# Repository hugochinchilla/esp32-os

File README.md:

# Chinchilla (esp32-os)

A 90s-style desktop operating environment (think Windows 95/98) for the
ESP32-S3, with VGA output from GPIO pins, Wi-Fi, and USB keyboard and mouse.

Status: **the desktop runs on the board.** Overlapping, resizable windows in
the 98 look with menus, a taskbar with a clock and the Start menu, desktop
icons, widgets, an Editor, a File manager, a Picture viewer (BMP, PNG,
baseline JPEG, GIF) and a drawing program, files on the flash (LittleFS, kept across restarts), a
start-up self-test, plus a debug protocol for screenshots,
injected input and file transfer.

## Try it in the browser

**<https://www.hugochinchilla.net/esp32-os/>**

The same desktop, running in a web page with nothing to install. It needs a
mouse and a keyboard. Files saved on its C: stay in your own browser. It is
built from `main` on every change; how it works is under
[Chinchilla in a web browser](#chinchilla-in-a-web-browser).

## What it will be

- 640x480 at 60 Hz on a VGA monitor, 256 colours, with a mouse cursor that
  always moves at 60 Hz.
- A desktop with taskbar, Start menu, icons and overlapping windows.
- A file system with a file manager, a Notepad-style text editor, and a viewer
  for BMP, PNG, JPEG and GIF images.
- Wi-Fi, with the clock set from NTP, or from an optional battery-backed clock
  chip.
- Vizcacha, a web browser for pages as the 1990s wrote them: no scripts, no
  style sheets, plain HTTP. [FrogFind](http://frogfind.com/) is its way into
  today's web.
- A serial debug protocol (screen capture, injected keyboard and mouse events)
  so the OS can be tested by an agent without a human.
- Remote keyboard, mouse and screen over the network until USB input hardware
  exists.

## Hardware

- ESP32-S3 dev board with 16 MB flash and 8 MB octal PSRAM (ESP32-S3-N16R8,
  DevKitC-1 pin layout, two USB-C sockets).
- An adapter board built on a 5x7 cm perfboard that the dev board plugs into:
  9 colour resistors and 2 sync resistors for VGA, an audio output filter for a
  3.5 mm jack, and a beeper.

See [docs/hardware/README.md](docs/hardware/README.md) for the pin map, the
resistor values and build notes.

## Repository layout

| Path | Contents |
| --- | --- |
| `docs/DECISIONS.md` | The index of what has been decided, what was rejected, and what is still open: what always applies, and one line per decision |
| `docs/decisions/` | One file per decision, listed in the index by `tools/decisions_index.py` |
| `docs/hardware/` | VGA adapter pin map, resistor values and board diagram |
| `docs/debug-protocol.md` | The serial protocol for screenshots and injected input |
| `docs/benchmark.md` | How to run the 60 fps benchmark again and read its results |
| `core/` | The portable part of the OS (C++). Depends on no hardware; builds for the board and for a PC |
| `firmware/os/` | The OS firmware: ESP-IDF project with the ESP32 adapters for `core/` |
| `firmware/vga-test/` | ESP-IDF test program for the VGA wiring |
| `host/` | PC build: unit tests and picture tests for `core/`, a simulated board, and `desktop/`, Chinchilla as a desktop program for Linux |
| `third_party/` | Freely licensed files from elsewhere: the Spleen font; the engine of Doom (GPL 2), which is part of `programs/doom` only |
| `web/` | Chinchilla in a web browser: the Emscripten build of `host/desktop/` and its page |
| `ci/` | GitHub Actions workflows to copy into `.github/workflows/`: the build, publishing the browser version on GitHub Pages, and deploying its relay to Cloudflare |
| `tools/` | `dbg.py`, the debug tool; `check_pictures.py`, the picture tests; `gen_font.py`, the font table generator; `mockup/`, the script that drew the target look; the setup script for Arch-based systems; the script that regenerates the board diagram |

## Tests on the PC

No board needed. Requires CMake, a C++ compiler, Python 3 and pyserial.

```sh
cmake -S host -B build/host
cmake --build build/host
ctest --test-dir build/host --output-on-failure
```

`build/host/sim` is a simulated board: it prints a port name that
`tools/dbg.py --port <name>` can talk to. `build/host/sim <folder>` also shows
that folder of the PC as drive D:.

The picture tests draw the desktop through a series of steps and compare
each screen with `host/tests/pictures/`. After an intended change to the
look, regenerate them, look at every changed picture, and commit them:

```sh
python3 tools/check_pictures.py build/host/render_scenes --update
```

The font table `core/src/gfx/font_spleen6x12.cpp` is generated:
`python3 tools/gen_font.py third_party/fonts/spleen/spleen-6x12.bdf core/src/gfx/font_spleen6x12.cpp`.

## The command shell on a PC

Chinchilla's command shell (`dir`, `ls`, `type`, `copy`, `ps`, `kill`...) in
a terminal of the PC. It is the same code that will run on the board's serial
port and in a terminal window; here the PC's terminal is the device. Needs
only CMake and a C++ compiler.

```sh
cmake -S host -B build/host && cmake --build build/host --target chinchilla-console
build/host/chinchilla-console                 # C: is a RAM disk with the sample files
build/host/chinchilla-console ~/some/folder   # that folder is C:, for real
```

`help` lists the commands. The line editing, the up arrow and Ctrl+C are
Chinchilla's own, not the PC's. Ctrl+D or `exit` leaves.

## Chinchilla as a desktop program (Linux)

The same `core/` in a window on a PC: the window is the monitor, the PC's
mouse and keyboard are the board's, and a folder of the PC is drive C:. For
trying programs without flashing, and for showing Chinchilla to someone with
no board. It is not an emulator of the ESP32: no memory limits, no real
Wi-Fi, and far faster than the board, so it says nothing about speed, RAM or
the colours on a real monitor.

Needs CMake, a C++ compiler and SDL2 with its headers:

| System | Install |
| --- | --- |
| Arch, Omarchy | `sudo pacman -S --needed cmake gcc make sdl2` (on a current Arch this installs `sdl2-compat`) |
| Debian, Ubuntu | `sudo apt install cmake g++ make libsdl2-dev` |
| Fedora | `sudo dnf install cmake gcc-c++ make SDL2-devel` |

```sh
cmake -S host -B build/desktop -DHOST_SANITIZE=OFF -DCMAKE_BUILD_TYPE=Release
cmake --build build/desktop --target chinchilla
build/desktop/chinchilla
```

The result is one file of about 1 MB, `build/desktop/chinchilla`. It runs on
another Linux PC with the same kind of processor that has SDL2 installed
(most desktops do).

| Option | What it does |
| --- | --- |
| `--drive FOLDER` | The folder that is drive C:. Default `~/.local/share/chinchilla/C`. A new, empty folder gets the sample files. They are ordinary files: copy a picture in from Linux and the File manager shows it |
| `--fast` | No start-up screens (a key or a click also skips them) |
| `--scale N` | Open the window at N times 640x480. Default: the largest of 1, 2, 3 that fits the desktop |
| `--fullscreen` | Start on the whole screen |
| `--mute` | No sound. Without it the self-test ends in a beep, the desktop comes up with a chime and message boxes knock, through the PC's sound card |

In the window:

- The window can be any size. The picture keeps its 4:3 shape, with black
  bars where it does not fill the window.
- F11 switches between the window and the whole screen. F12 saves a picture
  of the window as `chinchilla-001.bmp`, `-002` and so on in the folder the
  program was started from.
- Ctrl+Alt+End is Chinchilla's Ctrl+Alt+Del (Linux keeps the real one), and
  Ctrl+Esc opens the Start menu if the desktop keeps the Super key (which
  also means Super+D, Chinchilla's "show the desktop", may not arrive).
- Keys type what a US keyboard would: the core has no other layouts yet,
  the same as on the board.
- Closing the window shuts Chinchilla down: programs are asked to close, so
  the Editor still asks about unsaved text. Closing it again within three
  seconds leaves at once.
- There is no sound: the system does not make any yet, on the board either.

`build/host/chinchilla`, built along with the tests when SDL2 is installed,
is the same program with the memory checks on: some ten times larger, and
slower.

## Chinchilla in a web browser

The desktop program again, built to WebAssembly: a page that anyone can open,
with nothing to install. The page is the monitor, C: is kept in the visitor's
own browser (nothing is sent anywhere), and it comes back on the next visit.
It needs a mouse and a keyboard; it is not made for phones.

Needs [Emscripten](https://emscripten.org/docs/getting_started/downloads.html)
(tested with 7.0.0) and CMake. Emscripten downloads its own SDL2 the first
time.

```sh
emcmake cmake -S web -B build/web
cmake --build build/web
python3 -m http.server -d build/web/site 8080    # then open http://localhost:8080/
```

The result is one file, `build/web/site/index.html` (about 1.7 MB, 0.6 MB as
web servers send it). Put it on any web server, or send the file itself: it
also works opened straight from a folder.

To publish it on GitHub Pages on every change to `main`, copy
`ci/github-pages-workflow.yml` to `.github/workflows/pages.yml` and choose
Settings > Pages > Source: "GitHub Actions". The address is then
`https://<owner>.github.io/<repository>/`.

The page reaches the web through a relay, because a page may not open
connections of its own: `web/relay/README.md` says how to put it on
Cloudflare and give the page its address.

The page starts switched off, with a power button: a browser plays no sound
on a page nobody has clicked, and the self-test's beep and the welcome chime
are the first things the machine does.

What differs from the desktop program: the browser keeps some keys for itself
(Ctrl+W, Ctrl+T, F5, F11 and others; Ctrl+Alt+End is still Ctrl+Alt+Del),
Restart loads the page again, and in a private window C: lasts only until
the page is closed. `tools/test_web_page.js` drives the page in a real
browser (Node and Playwright).

## Building the VGA test

Needs [ESP-IDF](https://docs.espressif.com/projects/esp-idf/en/stable/esp32s3/get-started/)
v5.5. On Arch-based systems (including Omarchy), `tools/setup-arch.sh` installs
it together with the build tools and gives your user access to serial ports
without sudo. Log out and back in afterwards, then run `get_idf` in each new
terminal.

```sh
cd firmware/vga-test
idf.py set-target esp32s3
idf.py -p <serial port> flash monitor
```

Plug the computer into the USB-C socket marked UART (or COM). Details and the
keys that switch modes are in
[firmware/vga-test/README.md](firmware/vga-test/README.md).

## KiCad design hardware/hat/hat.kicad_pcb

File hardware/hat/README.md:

# Chinchilla hat v0.3 (prototype PCB)

A two-layer, 100 x 78 mm board that the ESP32-S3-DevKitC-1 plugs into. It
replaces the hand-built perfboard adapter and adds the extras Hugo chose on
2026-11-16. It is laid out for **partial assembly** (level B below): the
board maker places only 8 different SMD parts, and everything that is quick
to solder by hand is left to you. Version 0.3 puts every socket at a board
edge, facing outwards, so the board fits a 3D-printed case with cut-outs in
the walls (see [Enclosure](#enclosure)).

- VGA: 3-bit resistor ladders built from 1 k resistors only. Top bit: two 1 k
  in parallel (500 ohm); middle bit: one 1 k; low bit: two 1 k in series
  (2 k). Exact 1:2:4 steps, 0.69 V into 75 ohm at full white (the perfboard's
  510 / 1 k / 2 k gives 0.68 V). Sync lines through two 1 k in parallel
  (500 ohm instead of 100). Same pins as
  [the perfboard adapter](../../docs/hardware/README.md).
- Audio out (1 k + 100 nF filter, 10 uF DC block) to a through-hole 3.5 mm
  jack on the back edge, and a 2-pin header for a piezo between 3V3 and
  GPIO14.
- Clock chip DS3231MZ on I2C (GPIO1 SDA, GPIO2 SCL), alarm/1 Hz output on
  GPIO11, CR2032 holder.
- microSD socket wired for 1-bit SDMMC (CLK 39, CMD 40, D0 41), all data
  lines pulled up, card detect switch on GPIO12.
- USB host through a CH334R four-port hub (through-hole 12 MHz crystal) with
  four USB-A sockets in two stacked pairs: one pair on the back edge, one on
  the front edge. Room for keyboard, mouse and for example a USB Ethernet
  adapter. All four ports share the 0.5 A of the power switch. Port power goes through a TPS2051C
  current-limited switch: on by default, GPIO21 low turns it off, GPIO42
  reads its overcurrent flag. ESD protection (USBLC6-2SC6) on every port,
  100 uF electrolytic on port power. Bus powered from the dev board's 5V pin.
- Monitor presence on GPIO47: VGA pin 5 (a ground pin, which the monitor
  joins to the other grounds) is pulled up to 3V3 through 10 k and reaches
  GPIO47 through 1 k. Low means a monitor or adapter is plugged in. The
  other four ground pins and the shell stay grounded. No DDC/EDID: it would
  need a level shifter, one more part type on every order (owner's choice,
  2026-11-17).
- A 470 uF electrolytic and a 100 nF capacitor across 3V3, next to the dev
  board sockets. The VGA levels are the 3.3 V rail divided by resistors, so
  the rail's dip during each Wi-Fi transmit burst showed as scanlines. On the
  perfboard the same pair removed them at 20 dBm (tested 2026-11-18).
- A 6-pin expansion header (3V3, GPIO38, 47, 48, 5V, GND), not fitted.
  GPIO47 is shared with the monitor presence sense.

Only two resistor values (1 k, 10 k) and two capacitor values (100 nF,
10 uF). Pull-ups stay at 10 k because the SD card specification asks for
10 k to 100 k.

### Who fits what

| Board maker (SMD, 8 different parts, 52 placements) | You (hand soldering) |
| --- | --- |
| 1 k and 10 k resistors, 100 nF and 10 uF capacitors (0603 / 0805) | Two 1x22 sockets for the dev board |
| CH334R hub (QSOP-16, 0.635 mm pitch) | HD15 VGA socket, two stacked USB-A sockets |
| DS3231MZ clock (SOIC-8) | microSD socket (SMD, 1.1 mm pitch) and CR2032 holder (SMD, big pads) |
| TPS2051C power switch, 4x USBLC6-2SC6 | 12 MHz HC-49 crystal, 100 uF electrolytic, 3.5 mm jack, 2-pin piezo header, 470 uF electrolytic |

The lists are `fab/hat-bom-assembly.csv` (send to the maker) and
`fab/hat-hand-solder.csv` (buy yourself). `fab/hat-pos-top.csv` holds only the
maker's parts.

**Status: routed, passes KiCad's design rule check (no errors and no
unconnected pads; only silkscreen warnings, mostly connector outlines at the
board edge), not built.** Treat
the first order as a test run of one to three boards.

| Top (copper and silkscreen) | Bottom (copper, seen from below) |
| --- | --- |
|  |  |

## Files

| File | What it is |
| --- | --- |
| `hat.kicad_pro`, `hat.kicad_sch`, `hat.kicad_pcb` | KiCad project (saved by KiCad 7; KiCad 8 and 9 open it and convert it) |
| `hat.kicad_sym`, `sym-lib-table` | The board's own symbols (dev board sockets, connectors) |
| `fab/hat-gerbers.zip` | Gerbers and Excellon drill files, for any board maker |
| `fab/hat-bom.csv` | Full bill of materials, with who fits each part |
| `fab/hat-bom-assembly.csv` | The board maker's part of the BOM |
| `fab/hat-hand-solder.csv` | Parts you buy and solder |
| `fab/hat-pos-top.csv` | Pick-and-place for the board maker's parts, top side |
| `fab/hat-schematic.pdf`, `fab/hat-assembly-top.pdf` | Schematic and assembly drawing |
| `enclosure.png`, `enclosure.svg`, `enclosure-cutouts.csv` | Case reference: outline, M3 holes, wall cut-outs |

Tracks are 0.25 mm (0.4 mm for power), clearance 0.2 mm, vias 0.6/0.3 mm,
so any standard two-layer process can make it. The tracks were laid by
Freerouting 1.9 (`build/hat.dsn` in, `build/hat.ses` out) and imported by
`gen_pcb.py`; `REROUTE=1 FREEROUTING_JAR=... python3 tools/hat_pcb/gen_pcb.py
route` routes again after a placement change (needs Java and `xvfb-run`).
Placement coordinates in `hat-pos-top.csv` are from the board's bottom-left
corner.

Everything is generated from one parts table by the scripts in
`tools/hat_pcb/` (`parts.py` is the netlist and BOM; `gen_sch.py`,
`gen_pcb.py`, `gen_outputs.py`, `gen_enclosure.py` and `gen_case.py` write the files). Change `parts.py` and run
them again rather than editing the netlist by hand in two places. The
schematic netlist is checked against `parts.py` when it is generated. Once
the board is edited by hand in KiCad, the KiCad files become the source and
the scripts should be retired.

## Layout

- Dev board on top, in two 1x22 sockets 25.4 mm apart (10 holes on the
  perfboard, which fits the board in use). Its USB-C sockets line up with the
  right edge, its antenna end points left, with no copper pour under the
  antenna.
- Back (bottom) edge: VGA at the left end, the stacked USB-A pair and the
  audio jack, all right-angle parts with their fronts at the edge. About
  22 mm of free wall between the VGA's right screw post and the USB-A
  socket, so a bulky VGA plug fits and its thumbscrews can be turned. The
  coin cell sits just above the VGA socket. Left edge: microSD. Right
  edge: the dev board's two USB-C sockets. Front (top) edge: the second
  USB-A pair, next to the hub. The piezo header sits inside.
- Ground: a pour on both layers. The VGA socket's five ground pins and both
  shell lugs go to it (on the perfboard, pin 10 alone gave no picture).
- Parts on the top side only.

## Before ordering

1. Check the header spacing of your dev board (25.4 mm between the two rows)
   and that pin 1 (3V3) is at the antenna end. Measure the distance from the
   centre of pin 22 (GND, the last pin at the USB end) to the front of the
   USB-C sockets. The layout assumes 5.0 mm (`DEVKIT_USB_OVERHANG` in
   `gen_pcb.py`, estimated from the board's 70 mm length), so that the
   sockets end flush with the board's right edge. If yours differs, change
   the value and re-run the scripts.
2. Upload the project and look at the assembler's 3D / placement preview,
   especially the polarity of U1 to U5. If the maker builds its BOM from the
   KiCad project (AISLER does), mark the hand-solder parts (J1 to J9, BT1,
   Y1, C12, C13) as "do not place" there; they are already left out of
   `hat-pos-top.csv`.
3. The VGA socket footprint is a generic KiCad one (Tonar/Amphenol style,
   pins 3.03 mm from the edge). If the assembler offers a different HD15
   part, compare its drawing with the footprint.
4. Sync now goes through 500 ohm instead of the perfboard's 100 ohm. If your
   VGA-to-HDMI adapter shows no picture, solder a 1 k across each sync pair
   (R16/R17 and R18/R19) to bring it to about 330 ohm, or bridge them.
5. Solder the low parts first (microSD socket, coin cell holder), then the
   crystal, headers and capacitor, then the sockets and connectors.

## Enclosure

The board is meant to sit on four M3 standoffs inside a printed case, with
openings in all four walls. Coordinates are in mm from the board's top-left
corner (as in the drawing); heights are above the board's top surface.

| Wall | Opening | Centre | Size (w x h) | Centre height |
| --- | --- | --- | --- | --- |
| Back | VGA D shell, plus two 3.5 mm holes 25 mm apart for the screw posts | x = 24.5 | 19 x 10 | 6.3 |
| Back | Stacked USB-A pair | x = 67.4 | 15 x 16 | 7.8 |
| Back | Audio jack | x = 85.5 | 7 x 7 | 3.0 |
| Front | Second stacked USB-A pair | x = 70.2 | 15 x 16 | 7.8 |
| Left | microSD slot (the card sticks out about 2.5 mm) | y = 15.5 | 13 x 2.5 | 1.0 |
| Right | Dev board USB-C pair, one slot for both, tall enough for a plug's body | y = 36.7 | 30 x 7.5 | 14.2 |

- Board 100 x 78 mm, 1.6 mm thick, 2 mm corner radius. M3 holes at
  (4, 3.8), (96, 3.8), (4, 74.2) and (96, 74.2).
- The tallest parts are the dev board on its sockets (about 16 mm) and the
  USB-A pair (about 16 mm), so allow at least 18 mm of inside height above
  the board, and 4 mm standoffs below it for the through-hole leads.
- The VGA, USB-A and jack fronts are at the board edge. A wall up to about
  2 mm thick works for all three; the VGA shell sticks out about 7 mm, so a
  thicker wall is fine there.
- The heights come from typical datasheet values and the usual socket stack
  (8.5 mm socket plus 2.5 mm header plastic under the dev board). Check them
  with real parts before printing, and print a test strip of the back wall
  first.
- `tools/hat_pcb/gen_enclosure.py` redraws this from the board file if the
  layout changes.

### First case model

| Board | Case, back | Exploded |
| --- | --- | --- |
|  |  |  |

`case/hat-case.scad` (OpenSCAD) is a first two-part case built from the
table above, with `case/hat-case-base.stl` and `case/hat-case-lid.stl` ready
to slice. More views are in `case/`. Outside size 105 x 83 x 27.6 mm.

- The tray has four 4 mm standoffs and walls up to the board's top surface.
- The lid carries the walls. Its slots are open at the bottom, so it drops
  over the sockets after the board and dev board are in. Four posts press the
  board onto the standoffs.
- Four M3 x 25 screws go through the roof, the posts and the board into the
  standoffs (2.8 mm holes for self-tapping; drill out for heat-set inserts).
- The VGA slot is 31.5 mm wide so the D shell and both screw posts pass.
- The parts on the board model are plain blocks sized from typical datasheet
  values. It is a fit check, not a tested print: nothing has been printed.
- `python3 tools/hat_pcb/gen_case.py render` rebuilds the model, the views
  and the STL files from the board (needs OpenSCAD and `xvfb-run`).

## Firmware notes

- Pins newly used: GPIO11 (clock chip alarm, open drain, pulled up),
  GPIO12 (card detect, low when a card is inserted) and GPIO47 (monitor
  presence, low when a monitor is plugged in). All three were spare.
  Untested with a VGA-to-HDMI adapter: check that it also grounds pin 5.
- Leave GPIO21 high or floating to keep USB power on (R30 pulls it up).
- The hub is a standard USB hub. ESP-IDF 5.5's USB host library supports
  external hubs behind `CONFIG_USB_HOST_HUBS_SUPPORTED` (marked
  experimental); check this before relying on it.

## Where to order in Europe

Prices checked 2026-11-16 where the maker publishes them; others are rough
estimates and say so. All take a KiCad project or Gerbers plus BOM and
pick-and-place, which is what `fab/` holds.

| Maker | Where | Minimum | Lead time | Files | Price |
| --- | --- | --- | --- | --- | --- |
| [AISLER](https://aisler.net/products/assembly) | Germany | 1 assembled board (bare boards in sets of 3) | 6 business days (Blitz); about 9 with part buying | Native KiCad project upload, BOM built automatically; Gerbers also accepted | Instant price on upload. Bare boards: EUR 12 + EUR 0.067/cm² per board, so 3 of these 78 cm² boards are about EUR 28 + VAT. Assembly fee and parts on top. Free shipping |
| [Eurocircuits](https://www.eurocircuits.com/pcb-assembly-proto/) | Belgium (plants in BE, DE, HU) | 1 board (PCB Proto: 1 to 5) | 6 working days assembled (3 + 3), faster options | Gerber/ODB++ plus BOM and CPL, data checked in their visualiser | Online calculator, no published examples; no minimum charge or tooling cost. My estimate: the dearest of the three for one-offs |
| [Beta Layout / PCB-POOL](https://eu.beta-layout.com/pcb/) | Germany / Ireland | 1 board (assembly of 1 to 50) | Boards from 8 h; assembly time in the configurator | Gerbers; other formats on their file format page | Configurator or quote |
| For comparison: [JLCPCB](https://jlcpcb.com/news/eu-customs-reform-2026) | China, ships to the EU | 2 assembled boards | About 1 to 2 weeks with shipping | Gerbers + BOM + CPL (the files in `fab/`) | Usually the cheapest. Since 1 July 2026 every EU parcel pays duty: EUR 3 per item category for private orders under EUR 150, plus VAT and a possible carrier fee |

### Estimated cost by assembly level

Rough estimates made on 2026-11-16, before VAT and before any quote, from
AISLER's last published fees (see below). The design in this folder is
level B. Levels C and D need small changes to the board (a through-hole fuse
instead of the switch, no ESD chips).

| Level | Board maker places | Different parts | 1 board | 3 boards | 6 boards | Your parts for 3 boards |
| --- | --- | --- | --- | --- | --- | --- |
| A (v0.1) | Everything | 23 | EUR 245 | EUR 310 | EUR 390 | none |
| **B (v0.2)** | Resistors, capacitors, hub, clock chip, power switch, ESD | 8 | EUR 115 | EUR 140 | EUR 200 | about EUR 50 |
| C | As B, without switch and ESD (you fit a through-hole fuse) | 6 | EUR 95 | EUR 120 | EUR 170 | about EUR 50 |
| D | As C, and you also solder the clock chip | 5 | EUR 80 | EUR 90 | EUR 120 | about EUR 70 |
| E | Nothing: bare boards and stencil | 0 | EUR 40 | EUR 40 | EUR 55 | about EUR 80 |

For comparison, JLCPCB at level B (four "extended" parts at $3, the rest
basic) comes to about EUR 85 for 2 boards and EUR 100 for 5 including the EU
import costs, so the gap to a German maker mostly closes. At level A it was
about EUR 115 for 3 against AISLER's EUR 310.

How they were worked out:

- **AISLER.** Their last published assembly fees (May 2022, may have
  changed) are EUR 7.50 per different part, EUR 0.04 per placed SMD part and
  EUR 0.01 per cm² per board. The per-part fee does not grow with
  quantity, which is why fewer different parts matter more than fewer parts. Add
  bare boards (EUR 12 + EUR 0.067/cm² per board, in sets of 3, about EUR 28
  for 3), a stencil (EUR 5 + EUR 0.095/cm², about EUR 12), parts and free
  shipping. Through-hole soldering prices are not published and are left out.
  Soldering the five through-hole parts yourself removes 5 different parts
  (about EUR 37) plus their soldering charge.
  ([fees](https://community.aisler.net/t/amazing-assembly-gets-radical-price-cuts/905),
  [boards and stencil](https://community.aisler.net/t/our-simple-pricing/102))
- **JLCPCB.** Economic assembly: about $8 setup, $1.50 stencil, $3 for each
  "extended" part type (about 8 here), $0.0164 per hand-soldered joint plus a
  $3.58 hand-soldering charge (about 76 joints), boards about $5, parts about
  $20 per board at LCSC prices, DHL to Spain about $20 to 25. Some parts
  (the Würth USB-A, Keystone holder, Amphenol VGA socket) may need LCSC
  equivalents. On delivery add VAT and, since 1 July 2026, EUR 3 duty per item
  category plus the carrier's handling fee, about EUR 25 to 40 in total.
  ([fees](https://jlcpcb.com/help/article/pcb-assembly-price),
  [EU duty](https://jlcpcb.com/news/eu-customs-reform-2026))
- **Eurocircuits.** Their 3-day PCB Proto price for two bare 100 x 80 mm
  boards was EUR 168 in October 2026
  ([comparison](https://deltaproto.com/pcb-assembly-netherlands-compared));
  assembly and parts come on top. Use their calculator before deciding.

Recommendation: **AISLER**. It is in Germany, takes the KiCad project
directly and shows a price before you pay, builds a single board, and buys
parts from LCSC, Mouser, Digi-Key, Farnell and others, so the CH334R (an LCSC
part) is available. ([parts sources](https://community.aisler.net/t/component-procurement-capabilities/2464),
[pricing](https://community.aisler.net/t/our-simple-pricing/102))

Multi-CB (Germany) makes bare boards and stencils quickly and imports KiCad
files, but assembly goes through a separate quote, so it suits a self-solder
build better.

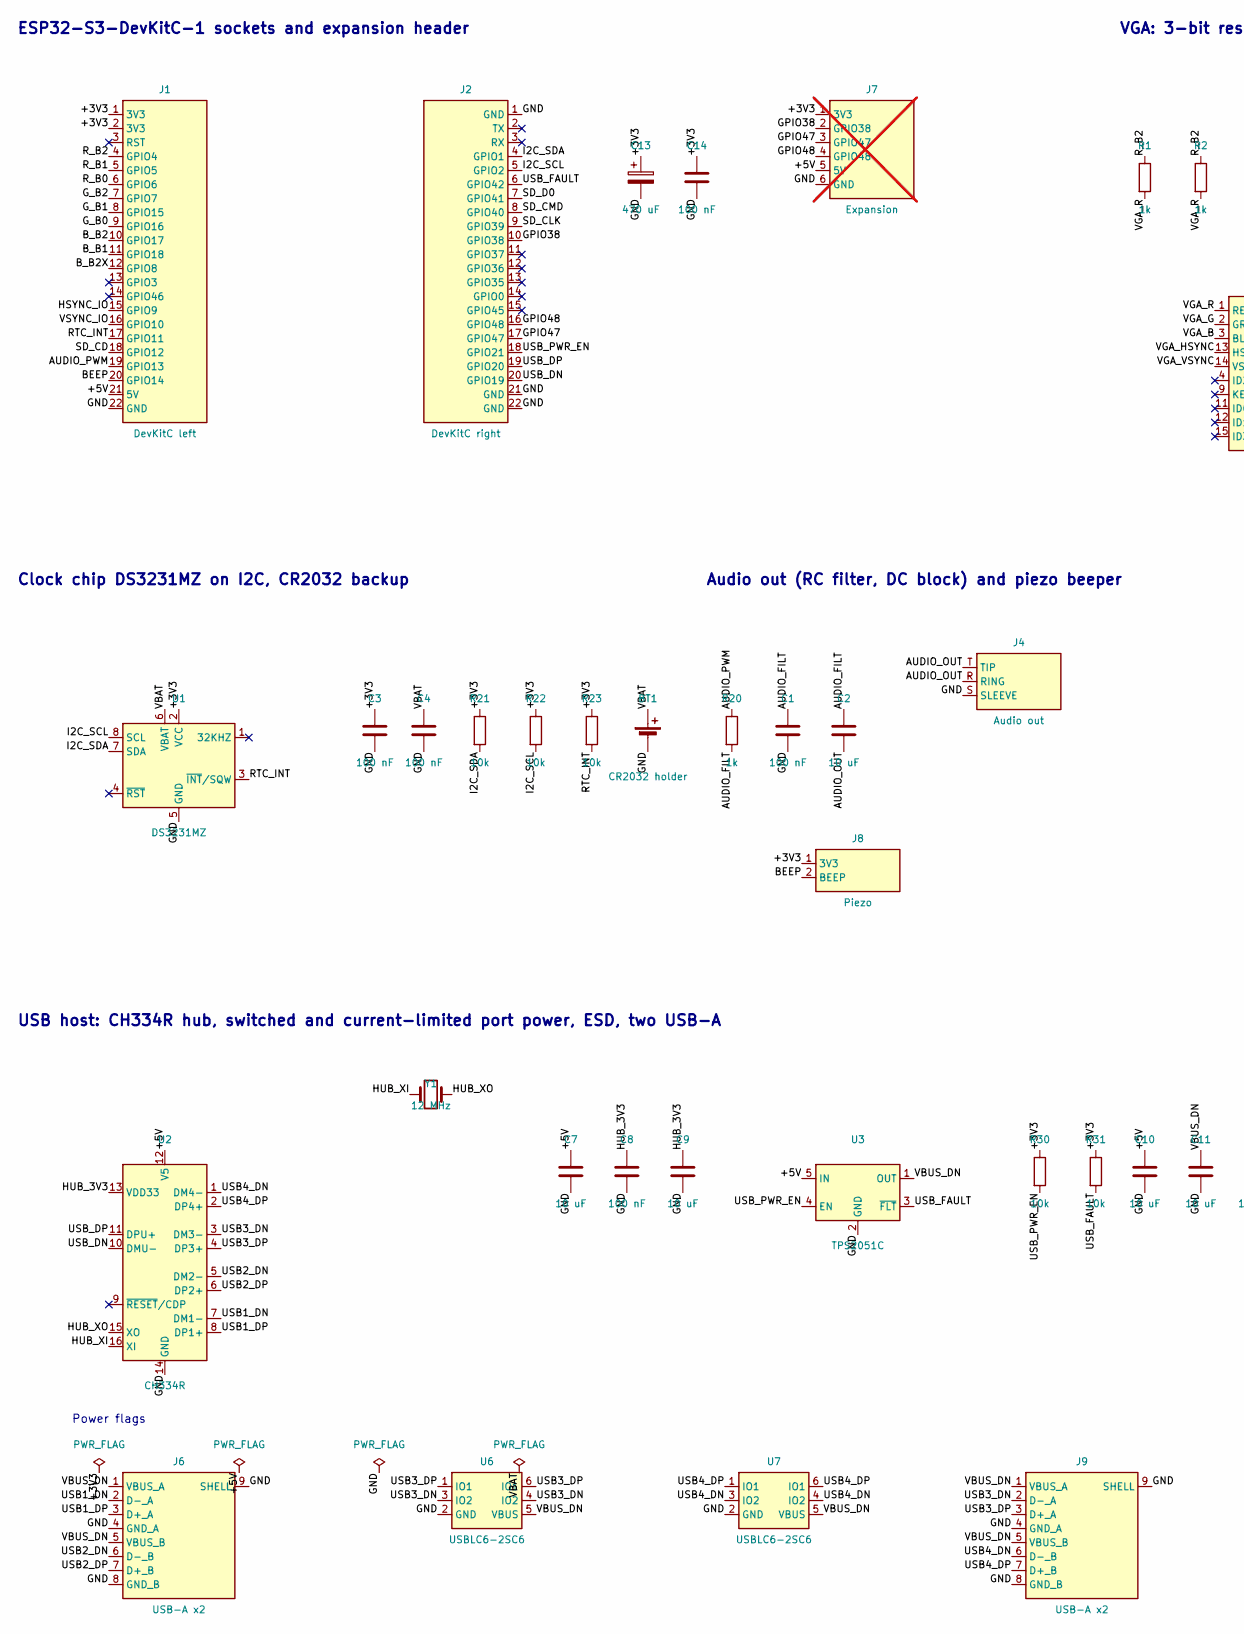
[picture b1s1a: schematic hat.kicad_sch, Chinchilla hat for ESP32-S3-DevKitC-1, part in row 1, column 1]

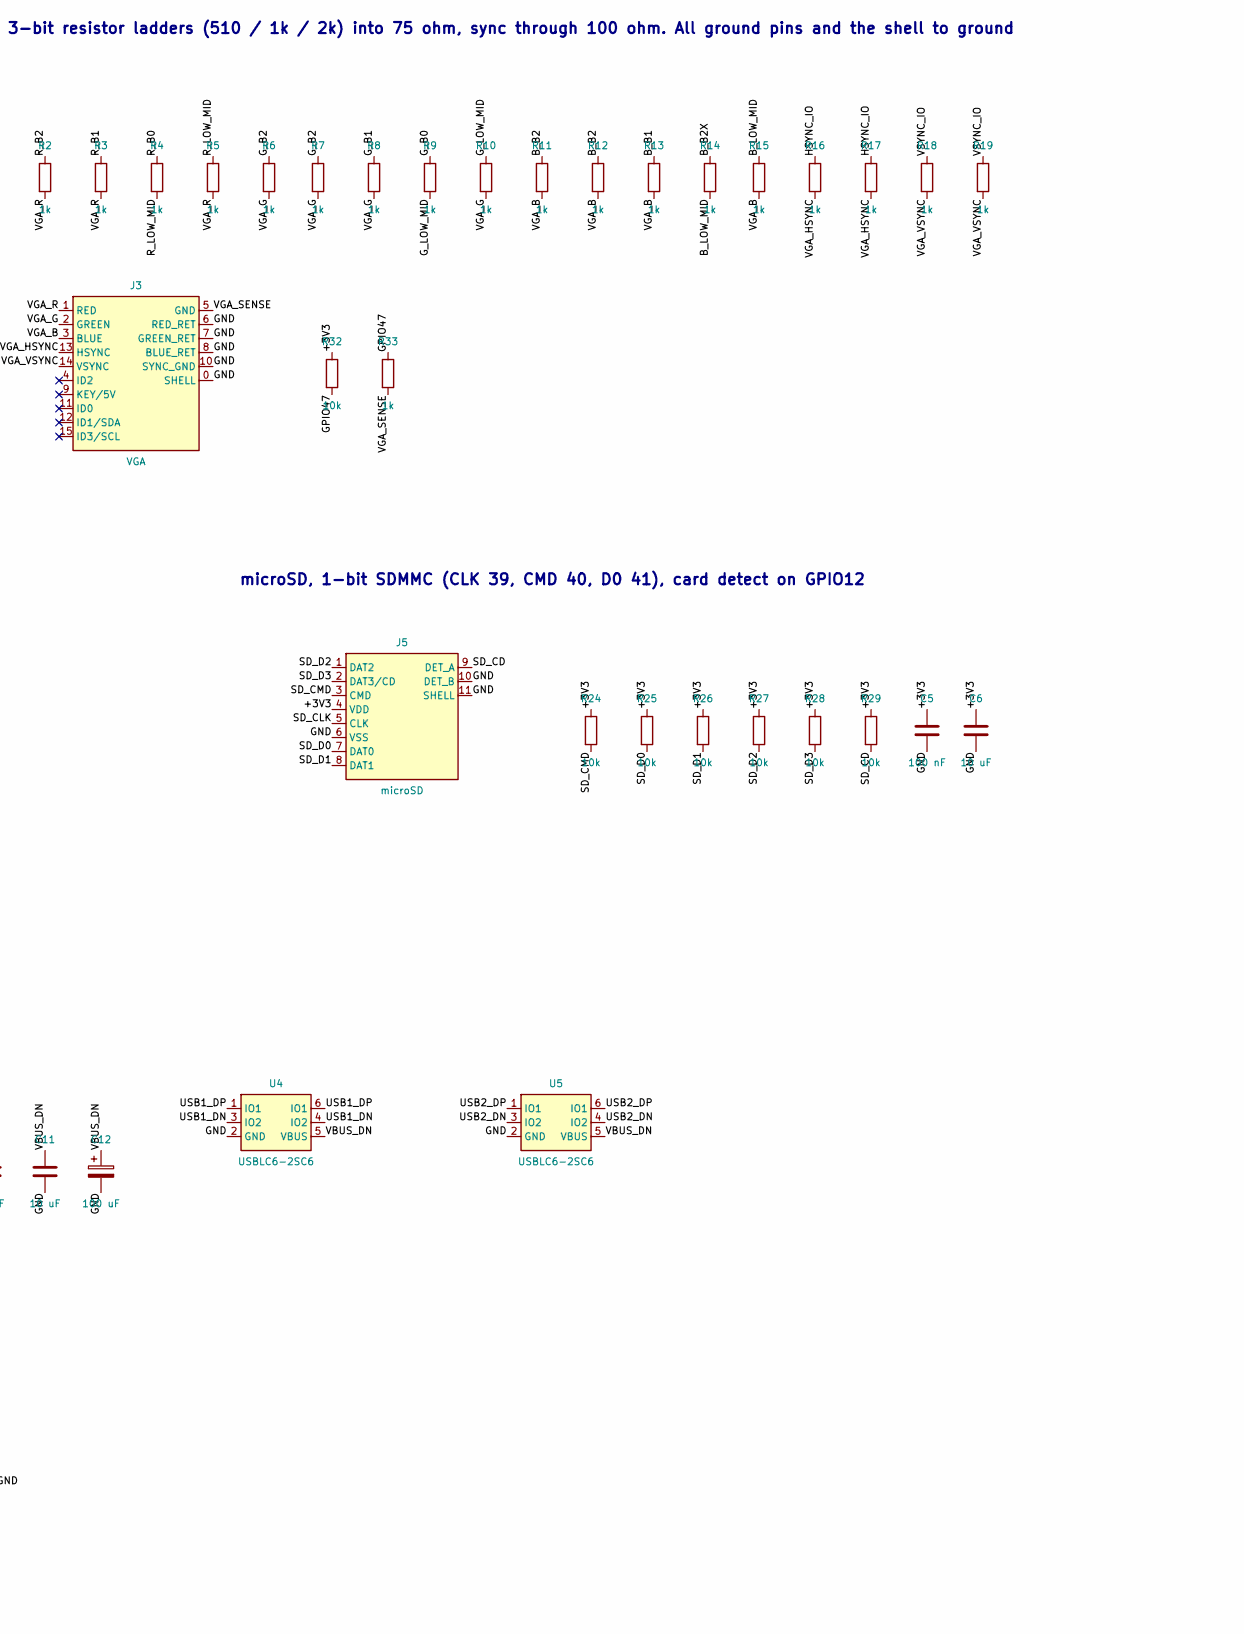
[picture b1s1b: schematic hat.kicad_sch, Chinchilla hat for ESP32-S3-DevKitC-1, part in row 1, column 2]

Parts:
BT1: CR2032 holder; BatteryHolder_Keystone_3034_1x20mm; MPN 3034
C1, C3, C4, C5, C8, C14: 100 nF; C_0603_1608Metric; MPN CL10B104KB8NNNC; LCSC C1591
C2, C6, C7, C9, C10, C11: 10 uF; C_0805_2012Metric; MPN CL21A106KAYNNNE; LCSC C15850
C12: 100 uF; CP_Radial_D6.3mm_P2.50mm
C13: 470 uF; CP_Radial_D8.0mm_P3.50mm
J1: DevKitC left; PinSocket_1x22_P2.54mm_Vertical; MPN 61302211821
J2: DevKitC right; PinSocket_1x22_P2.54mm_Vertical; MPN 61302211821
J3: VGA; DSUB-15-HD_Female_Horizontal_P2.29x1.98mm_EdgePinOffset3.03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; MPN L77HDE15SD1CH4F
J4: Audio out; Jack_3.5mm_CUI_SJ1-3523N_Horizontal; MPN SJ1-3523N
J5: microSD; microSD_HC_Molex_104031-0811; MPN 1040310811
J6, J9: USB-A x2; USB_A_Wuerth_61400826021_Horizontal_Stacked; MPN 61400826021
J7: Expansion; PinHeader_1x06_P2.54mm_Vertical; not fitted
J8: Piezo; PinHeader_1x02_P2.54mm_Vertical
R1, R2, R3, R4, R5, R6, R7, R8, R9, R10, R11, R12, R13, R14, R15, R16, R17, R18, R19, R20, R33: 1k; R_0603_1608Metric; MPN RC0603FR-071KL
R21, R22, R23, R24, R25, R26, R27, R28, R29, R30, R31, R32: 10k; R_0603_1608Metric; MPN RC0603FR-0710KL
U1: DS3231MZ; SOIC-8_3.9x4.9mm_P1.27mm; MPN DS3231MZ+TRL
U2: CH334R; QSOP-16_3.9x4.9mm_P0.635mm; MPN CH334R; LCSC C4154405
U3: TPS2051C; SOT-23-5; MPN TPS2051CDBVR
U4, U5, U6, U7: USBLC6-2SC6; SOT-23-6; MPN USBLC6-2SC6; LCSC C7519
Y1: 12 MHz; Crystal_HC49-U_Vertical

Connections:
+3V3: C3.1, C5.1, C6.1, C13.1, C14.1, J1.1 (3V3), J1.2 (3V3), J5.4 (VDD), J7.1 (3V3), J8.1 (3V3), R21.1, R22.1, R23.1, R24.1, R25.1, R26.1, R27.1, R28.1, R29.1, R30.1, R31.1, R32.1, U1.2 (VCC)
+5V: C7.1, C10.1, J1.21 (5V), J7.5 (5V), U2.12 (V5), U3.5 (IN)
AUDIO_FILT: C1.1, C2.1, R20.2
AUDIO_OUT: C2.2, J4.R (RING), J4.T (TIP)
AUDIO_PWM: J1.19 (GPIO13), R20.1
BEEP: J1.20 (GPIO14), J8.2 (BEEP)
B_B1: J1.11 (GPIO18), R13.1
B_B2: J1.10 (GPIO17), R11.1, R12.1
B_B2X: J1.12 (GPIO8), R14.1
B_LOW_MID: R14.2, R15.1
GND: BT1.2 (-), C1.2, C3.2, C4.2, C5.2, C6.2, C7.2, C8.2, C9.2, C10.2, C11.2, C12.2, C13.2, C14.2, J1.22 (GND), J2.1 (GND), J2.21 (GND), J2.22 (GND), J3.0 (SHELL), J3.6 (RED_RET), J3.7 (GREEN_RET), J3.8 (BLUE_RET), J3.10 (SYNC_GND), J4.S (SLEEVE), J5.6 (VSS), J5.10 (DET_B), J5.11 (SHELL), J6.4 (GND_A), J6.8 (GND_B), J6.9 (SHELL), J7.6 (GND), J9.4 (GND_A), J9.8 (GND_B), J9.9 (SHELL), U1.5 (GND), U2.14 (GND), U3.2 (GND), U4.2 (GND), U5.2 (GND), U6.2 (GND), U7.2 (GND)
GPIO38: J2.10 (GPIO38), J7.2 (GPIO38)
GPIO47: J2.17 (GPIO47), J7.3 (GPIO47), R32.2, R33.1
GPIO48: J2.16 (GPIO48), J7.4 (GPIO48)
G_B0: J1.9 (GPIO16), R9.1
G_B1: J1.8 (GPIO15), R8.1
G_B2: J1.7 (GPIO7), R6.1, R7.1
G_LOW_MID: R9.2, R10.1
HSYNC_IO: J1.15 (GPIO9), R16.1, R17.1
HUB_3V3: C8.1, C9.1, U2.13 (VDD33)
HUB_XI: U2.16 (XI), Y1.1
HUB_XO: U2.15 (XO), Y1.2
I2C_SCL: J2.5 (GPIO2), R22.2, U1.8 (SCL)
I2C_SDA: J2.4 (GPIO1), R21.2, U1.7 (SDA)
RTC_INT: J1.17 (GPIO11), R23.2, U1.3 (~INT/SQW)
R_B0: J1.6 (GPIO6), R4.1
R_B1: J1.5 (GPIO5), R3.1
R_B2: J1.4 (GPIO4), R1.1, R2.1
R_LOW_MID: R4.2, R5.1
SD_CD: J1.18 (GPIO12), J5.9 (DET_A), R29.2
SD_CLK: J2.9 (GPIO39), J5.5 (CLK)
SD_CMD: J2.8 (GPIO40), J5.3 (CMD), R24.2
SD_D0: J2.7 (GPIO41), J5.7 (DAT0), R25.2
SD_D1: J5.8 (DAT1), R26.2
SD_D2: J5.1 (DAT2), R27.2
SD_D3: J5.2 (DAT3/CD), R28.2
USB1_DN: J6.2 (D-_A), U2.7 (DM1-), U4.3 (IO2), U4.4 (IO2)
USB1_DP: J6.3 (D+_A), U2.8 (DP1+), U4.1 (IO1), U4.6 (IO1)
USB2_DN: J6.6 (D-_B), U2.5 (DM2-), U5.3 (IO2), U5.4 (IO2)
USB2_DP: J6.7 (D+_B), U2.6 (DP2+), U5.1 (IO1), U5.6 (IO1)
USB3_DN: J9.2 (D-_A), U2.3 (DM3-), U6.3 (IO2), U6.4 (IO2)
USB3_DP: J9.3 (D+_A), U2.4 (DP3+), U6.1 (IO1), U6.6 (IO1)
USB4_DN: J9.6 (D-_B), U2.1 (DM4-), U7.3 (IO2), U7.4 (IO2)
USB4_DP: J9.7 (D+_B), U2.2 (DP4+), U7.1 (IO1), U7.6 (IO1)
USB_DN: J2.20 (GPIO19), U2.10 (DMU-)
USB_DP: J2.19 (GPIO20), U2.11 (DPU+)
USB_FAULT: J2.6 (GPIO42), R31.2, U3.3 (~FLT)
USB_PWR_EN: J2.18 (GPIO21), R30.2, U3.4 (EN)
VBAT: BT1.1 (+), C4.1, U1.6 (VBAT)
VBUS_DN: C11.1, C12.1, J6.1 (VBUS_A), J6.5 (VBUS_B), J9.1 (VBUS_A), J9.5 (VBUS_B), U3.1 (OUT), U4.5 (VBUS), U5.5 (VBUS), U6.5 (VBUS), U7.5 (VBUS)
VGA_B: J3.3 (BLUE), R11.2, R12.2, R13.2, R15.2
VGA_G: J3.2 (GREEN), R6.2, R7.2, R8.2, R10.2
VGA_HSYNC: J3.13 (HSYNC), R16.2, R17.2
VGA_R: J3.1 (RED), R1.2, R2.2, R3.2, R5.2
VGA_SENSE: J3.5 (GND), R33.2
VGA_VSYNC: J3.14 (VSYNC), R18.2, R19.2
VSYNC_IO: J1.16 (GPIO10), R18.1, R19.1

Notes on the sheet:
ESP32-S3-DevKitC-1 sockets and expansion header
VGA: 3-bit resistor ladders (510 / 1k / 2k) into 75 ohm, sync through 100 ohm. All ground pins and the shell to ground
Audio out (RC filter, DC block) and piezo beeper
Clock chip DS3231MZ on I2C, CR2032 backup
microSD, 1-bit SDMMC (CLK 39, CMD 40, D0 41), card detect on GPIO12
USB host: CH334R hub, switched and current-limited port power, ESD, two USB-A
Power flags

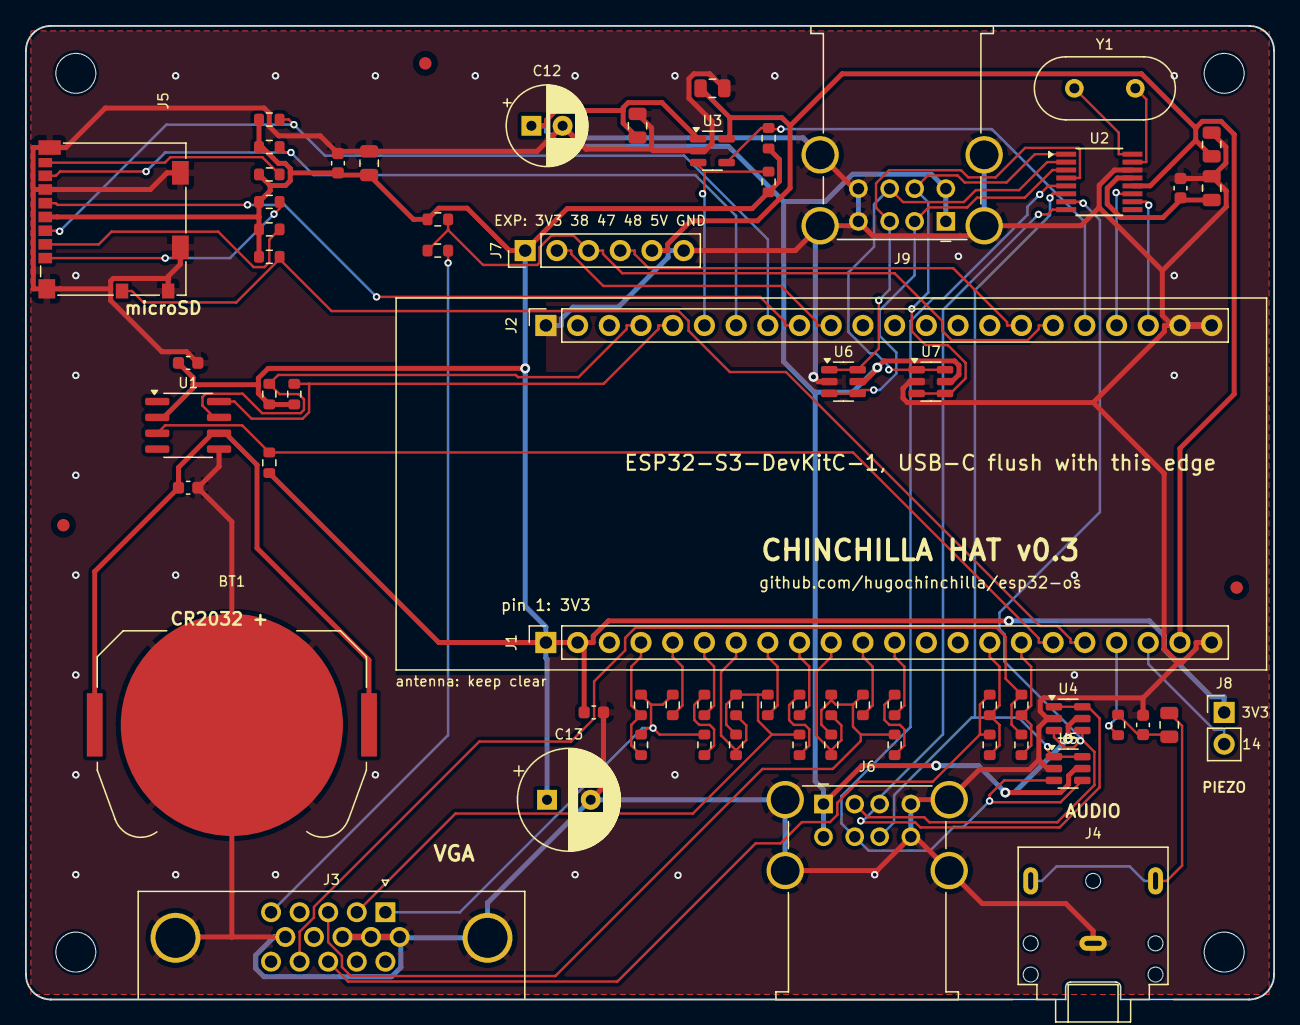
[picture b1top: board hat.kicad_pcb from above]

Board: 2 copper layers, 100.0 x 78.0 mm, 72 parts (0 on the bottom side), 57 nets.

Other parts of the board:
FID1, FID2, FID3: Fiducial_1mm_Mask2mm
H1, H2, H3, H4: MountingHole_3.2mm_M3

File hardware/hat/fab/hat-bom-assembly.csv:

Designator,Quantity,Value,Footprint,Manufacturer,MPN,LCSC,Description
"C1,C3,C4,C5,C8,C14",6,100 nF,C_0603_1608Metric,Samsung,CL10B104KB8NNNC,C1591,100 nF 50 V X7R 0603
"C2,C6,C7,C9,C10,C11",6,10 uF,C_0805_2012Metric,Samsung,CL21A106KAYNNNE,C15850,10 uF 25 V X5R 0805
"R1,R2,R3,R4,R5,R6,R7,R8,R9,R10,R11,R12,R13,R14,R15,R16,R17,R18,R19,R20,R33",21,1k,R_0603_1608Metric,YAGEO,RC0603FR-071KL,,Resistor 1k ohm 1% 0603
"R21,R22,R23,R24,R25,R26,R27,R28,R29,R30,R31,R32",12,10k,R_0603_1608Metric,YAGEO,RC0603FR-0710KL,,Resistor 10k ohm 1% 0603
U1,1,DS3231MZ,SOIC-8_3.9x4.9mm_P1.27mm,Analog Devices,DS3231MZ+TRL,,"RTC, I2C, MEMS resonator +-5 ppm, SOIC-8"
U2,1,CH334R,QSOP-16_3.9x4.9mm_P0.635mm,WCH,CH334R,C4154405,"USB 2.0 4-port hub controller, QSOP-16"
U3,1,TPS2051C,SOT-23-5,Texas Instruments,TPS2051CDBVR,,"USB power switch, 0.5 A, active-high enable"
"U4,U5,U6,U7",4,USBLC6-2SC6,SOT-23-6,STMicroelectronics,USBLC6-2SC6,C7519,USB ESD protection

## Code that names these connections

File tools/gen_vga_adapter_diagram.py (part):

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def y(r): return OY+(r-1)*P
LC=7; RC=17; R0=2
def hr(n): return y(n+R0-1)
J1=["3V3","3V3","RST","GPIO4","GPIO5","GPIO6","GPIO7","GPIO15","GPIO16","GPIO17","GPIO18","GPIO8","GPIO3","GPIO46","GPIO9","GPIO10","GPIO11","GPIO12","GPIO13","GPIO14","5V","GND"]
J3=["GND","TX","RX","GPIO1","GPIO2","GPIO42","GPIO41","GPIO40","GPIO39","GPIO38","GPIO37","GPIO36","GPIO35","GPIO0","GPIO45","GPIO48","GPIO47","GPIO21","GPIO20","GPIO19","GND","GND"]
RED="#c0392b"; GRN="#1e8449"; BLU="#1f5fa8"; GRY="#555"
slots={4:("510",RED),5:("1 k",RED),6:("2 k",RED),7:("510",GRN),8:("1 k",GRN),9:("2 k",GRN),10:("510",BLU),11:("1 k",BLU),12:("2 k",BLU),15:("100",GRY),16:("100",GRY)}
chan=[("RED","VGA pin 1",RED,4,6),("GREEN","VGA pin 2",GRN,7,9),("BLUE","VGA pin 3",BLU,10,12)]
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out(17,"GND  →  VGA pins 5 6 7 8 10","#000")
a(f'<text x="{x(1)-48}" y="{hr(4)-34}" text-anchor="end" font-size="13" fill="#444">pin header 1x14, wires to the VGA socket</text>')
# beeper wire (drawn first so parts sit on top)
# audio: 1 k on the GPIO13 row, 100 nF to ground, series capacitor to the jack pin
yy=hr(19)
a(f'<line x1="{x(2)}" y1="{yy}" x2="{x(6)}" y2="{yy}" stroke="#888" stroke-width="3"/>')
a(f'<rect x="{x(3)-8}" y="{yy-11}" width="{2*P+16}" height="22" rx="9" fill="#f3e3c0" stroke="{ORG}" stroke-width="3"/>')
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dot(3,13,REDW); dot(3,14,"#111"); dot(3,22,"#111")
a(f'<text x="{x(1)-20}" y="{(hr(13)+hr(14))/2-3}" text-anchor="end" font-size="13" fill="{REDW}" font-weight="bold">100 to 470 µF, + up</text>')
a(f'<text x="{x(1)-20}" y="{(hr(13)+hr(14))/2+13}" text-anchor="end" font-size="12" fill="#444">3V3 to GND</text>')
# beeper between 3V3 and GPIO14
bridge(6,1,7,1); bridge(3,1,3,2)
a(f'<circle cx="{(x(3)+x(6))/2}" cy="{hr(1)}" r="{P*2.0}" fill="#222" fill-opacity="0.82" stroke="#000" stroke-width="2"/>')
a(f'<circle cx="{(x(3)+x(6))/2}" cy="{hr(1)}" r="7" fill="#555"/>')
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a(f'<line x1="60" y1="{ly+74}" x2="100" y2="{ly+74}" stroke="#111" stroke-width="7" stroke-dasharray="2 5"/><text x="112" y="{ly+79}" font-size="15">bare wire along the GND row, soldered at every hole it passes (the ground rail)</text>')
for k,t in enumerate(["Video: each colour has 510 Ω, 1 kΩ and 2 kΩ joined at their left ends. The rows of GPIO3 and GPIO46 stay empty.",
 "Audio: GPIO13 through 1 kΩ. The 100 nF capacitor goes from that point to ground, the 1 to 10 µF capacitor (+ towards the resistor) to AUDIO OUT.",
 "Beeper: between 3V3 and GPIO14, for a piezo beeper of about 10 mm; a 12 mm one overhangs the edge a little. A magnetic or 5 V buzzer needs a transistor instead.",
 "Supply capacitor: 100 to 470 µF, 10 V or more, + to the second 3V3 pin, − to the ground rail. Stand it a little above the resistors if it is wide.",
 "VGA ground: the three colour returns (pins 6, 7, 8), the sync ground (pin 10) and the cable's shield all go to the GND pin or the ground rail, as far as the cable has them.",
 "The right socket strip is drawn 10 holes from the left one; if your board is 9 apart, use column 16.",
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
